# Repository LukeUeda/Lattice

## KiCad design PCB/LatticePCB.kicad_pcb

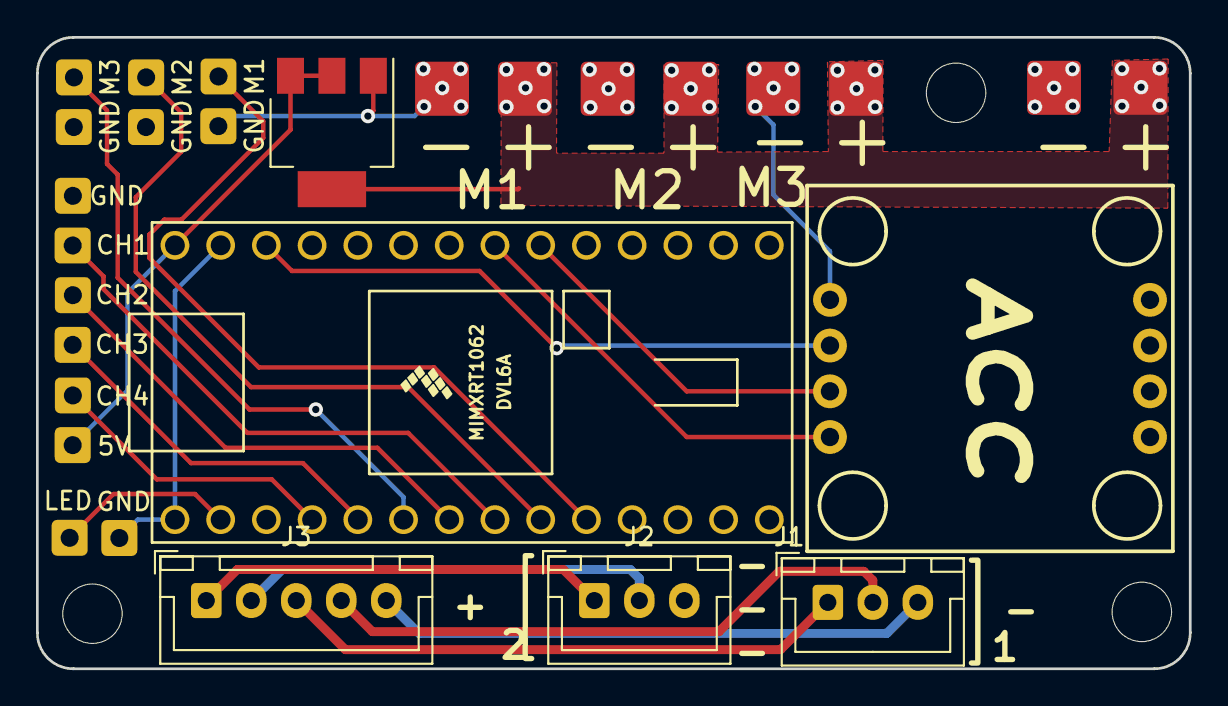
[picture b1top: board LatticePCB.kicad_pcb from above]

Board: 2 copper layers, 64.1 x 35.1 mm, 20 parts (0 on the bottom side), 10 nets.

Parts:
5V: GND; SolderWire-0.1sqmm_1x01_D0.4mm_OD1mm
CH1, CH3: GND; SolderWire-0.1sqmm_1x01_D0.4mm_OD1mm
CH2, CH4: M3; SolderWire-0.1sqmm_1x01_D0.4mm_OD1mm
GND: M3; SolderWire-0.1sqmm_1x01_D0.4mm_OD1mm
GND#2, GND#3, GND#4, GND#5: GND; SolderWire-0.1sqmm_1x01_D0.4mm_OD1mm
J1, J2: Conn_01x03_Pin; JST_XH_B3B-XH-A_1x03_P2.50mm_Vertical
J3: Conn_01x05_Pin; JST_XH_B5B-XH-A_1x05_P2.50mm_Vertical
LED: M3; SolderWire-0.1sqmm_1x01_D0.4mm_OD1mm
LIS331DLH1: lis331dlh
M1: M1; SolderWire-0.1sqmm_1x01_D0.4mm_OD1mm
M2: M2; SolderWire-0.1sqmm_1x01_D0.4mm_OD1mm
M3: M3; SolderWire-0.1sqmm_1x01_D0.4mm_OD1mm
U1: Teensy++1.0_(Arduino); Teensy40
U2: AMS1117CS-5.0; SOT-223

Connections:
GNDREF: GND.1, GND#2.1, GND#3.1, GND#4.1, GND#5.1, LIS331DLH1.4 (GND), U1.1 (GND), U1.32 (GND), U2.1 (GND)
unnamed: J1.1, J3.3
unnamed: J1.2, J3.4
unnamed: J1.3, J3.5
unnamed: J2.1, J3.1
unnamed: J2.2, J3.2
unnamed: LIS331DLH1.3 (3.3V), U1.31 (3.3V)
unnamed: LIS331DLH1.1 (SCL), U1.26 (19_(SCL))
unnamed: LIS331DLH1.2 (SDA), U1.25 (18_(SDA))
unnamed: 5V.1, U1.33 (VIN), U2.2 (VO), U2.3 (VO)

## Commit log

2023-12-22 Add pcb files
2023-12-23 Yeet
2023-12-23 Balance chargine ports added
